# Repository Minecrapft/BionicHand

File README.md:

# Robohand

A simple Arduino sketch to control a robotic hand (servo-based) — provided as `Robohand.ino`.

## Summary

This project contains an Arduino sketch that reads inputs (sensors/buttons/potentiometers) and drives servos to move a robotic hand. Use this README to set up the hardware, upload the sketch, and customize pin mappings or servo ranges.

## Files

- `Robohand.ino` — main Arduino sketch (open in Arduino IDE).

## Required Hardware

- Arduino board (Uno, Nano, Mega, etc.)
- 3–5 x hobby servos (depending on hand design)
- Power supply for servos (separate 5–6V recommended)
- Jumper wires, breadboard
- Optional: potentiometers, push buttons, flex sensors for control

## Wiring (example)

- Connect servo signal wires to Arduino digital pins (example):
  - Thumb: D3
  - Index: D5
  - Middle: D6
  - Ring: D9
  - Pinky: D10
- Connect servo power (V+) and ground to the servo power supply. Connect servo ground to Arduino GND.
- Connect control inputs (potentiometers or buttons) to analog pins A0–A2 as needed.

Adjust pin numbers in `Robohand.ino` to match your wiring.

## Software & Upload

1. Install the Arduino IDE from https://arduino.cc.
2. Open `Robohand.ino` in the Arduino IDE.
3. Select the correct board and port under `Tools` → `Board` / `Port`.
4. Connect the Arduino via USB and click Upload.

If using external servo power, ensure the external supply is connected and common-grounded with the Arduino before powering servos.

## Usage

- Once uploaded, control the hand using the configured inputs (potentiometers/buttons). The sketch maps inputs to servo positions; modify the mapping in the code if needed.

## Customization

- Open `Robohand.ino` and edit pin definitions and servo limits to match your hardware.
- Calibrate servo min/max values to prevent mechanical binding.

## Troubleshooting

- Servos jittering: provide a stable external power supply and common ground.
- Servo not moving: check signal pin, correct power, and that the sketch references the correct pin.

## Contact

If you want help customizing the sketch or wiring, open an issue or reply here.

## ESP32-S3 (connection & run)

This sketch can run on an ESP32-S3-based board with a few small changes. Follow these steps to connect and upload:

1. Install ESP32 board support in the Arduino IDE:
  - Open `Tools` → `Board` → `Boards Manager` and install the "esp32" package by Espressif.
2. Power and wiring:
  - Servos typically need 5V. Use a separate 5–6V servo power supply and connect all grounds together (ESP32 GND ↔ servo power GND).
  - Connect each servo signal wire to a free ESP32-S3 GPIO. Example (change pins in the sketch to match):
    - Thumb: GPIO 18
    - Index: GPIO 19
    - Middle: GPIO 21
    - Ring: GPIO 22
    - Pinky: GPIO 23
  - Avoid pins reserved for flash/SPI (commonly GPIO6–GPIO11) and consult your board's pinout for S3-specific restrictions.
3. Library and code changes:
  - If `Robohand.ino` uses the AVR `Servo.h`, switch to an ESP32-compatible servo library such as `ESP32Servo` (install via Library Manager) or use a PWM/i2c driver (PCA9685) for many servos.
  - Update the pin definitions at the top of `Robohand.ino` to the GPIOs you wired.
  - Ensure servo pulse limits are appropriate for your servos (calibrate `min`/`max` values to avoid binding).
4. Uploading the sketch:
  - In Arduino IDE select `Tools` → `Board` → `ESP32S3 Dev Module` (or the specific board name) and the correct `Port`.
  - Click Upload. If required, press the boot/enable buttons as prompted by the IDE.
5. Troubleshooting & tips:
  - If servos twitch or reset the board, power them from a dedicated supply and keep a common ground.
  - For many servos, using a dedicated PWM driver (PCA9685) reduces load on the ESP32 and simplifies timing.
  - Use the Serial Monitor to view debug messages; set the baud rate in the sketch to match (commonly 115200).

These steps should get `Robohand.ino` running on an ESP32-S3 board. If you want, I can update `Robohand.ino` to include `ESP32Servo` examples and default ESP32 pin definitions.

## Control via Phone (Web Interface)

To control the robot hand from your phone using a web browser on the local network:

### Setup

1. **Connect ESP32-S3 to WiFi:**
   - Add WiFi credentials to `Robohand.ino`:
     ```cpp
     const char* ssid = "YOUR_WIFI_SSID";
     const char* password = "YOUR_WIFI_PASSWORD";
     ```
   - Initialize WiFi in `setup()`:
     ```cpp
     WiFi.begin(ssid, password);
     while (WiFi.status() != WL_CONNECTED) {
       delay(500);
     }
     Serial.println(WiFi.localIP());
     ```
   - Note the IP address printed to the Serial Monitor (e.g., `192.168.1.100`).

2. **Create a simple web server:**
   - Add these includes at the top of `Robohand.ino`:
     ```cpp
     #include <WiFi.h>
     #include <WebServer.h>
     ```
   - Create a WebServer instance:
     ```cpp
     WebServer server(80);  // Listen on port 80 (HTTP)
     ```
   - In `setup()`, define a handler that serves an HTML control panel:
     ```cpp
     server.on("/", HTTP_GET,  {
       String html = "<html><body style='font-family:Arial'>"
         "<h1>Robohand Control</h1>"
         "<button onclick=\"fetch('/servo?pin=18&pos=90')\">Thumb Open</button>"
         "<button onclick=\"fetch('/servo?pin=18&pos=0')\">Thumb Close</button><br>"
         "<button onclick=\"fetch('/servo?pin=19&pos=90')\">Index Open</button>"
         "<button onclick=\"fetch('/servo?pin=19&pos=0')\">Index Close</button><br>"
         "</body></html>";
       server.send(200, "text/html", html);
     });
     ```
   - Add a servo control endpoint:
     ```cpp
     server.on("/servo", HTTP_GET,  {
       int pin = server.arg("pin").toInt();
       int pos = server.arg("pos").toInt();
       // Attach servo and move to position
       // (details depend on your Servo library)
       server.send(200, "text/plain", "OK");
     });
     ```
   - Start the server in `setup()`:
     ```cpp
     server.begin();
     ```
   - In `loop()`, handle incoming requests:
     ```cpp
     server.handleClient();
     ```

3. **Access from your phone:**
   - Connect your device to the **`RoboHand-S3`** WiFi network (password: `12345678`).
   - Open a web browser and navigate to: **`http://192.168.4.1`**
   - No port number needed — it runs on port 80 (standard HTTP), so the browser uses it automatically.
   - You should see the Robohand control panel with buttons to open/close fingers.

4. **Customize the web interface:**
   - Add sliders for smooth servo control:
     ```html
     <input type="range" min="0" max="180" value="90" 
       onchange="fetch('/servo?pin=18&pos=' + this.value)">
     ```
   - Add visual feedback (color change, status display) using JavaScript.

### Troubleshooting

- **Phone can't find the ESP32:** Ensure both phone and ESP32-S3 are on the same WiFi network.
- **Web page doesn't load:** Check the IP address from the Serial Monitor (e.g., 192.168.1.), and make sure no firewall is blocking port 80.
- **Servos don't respond:** Verify the `/servo` endpoint is correctly wired to your servo control code.

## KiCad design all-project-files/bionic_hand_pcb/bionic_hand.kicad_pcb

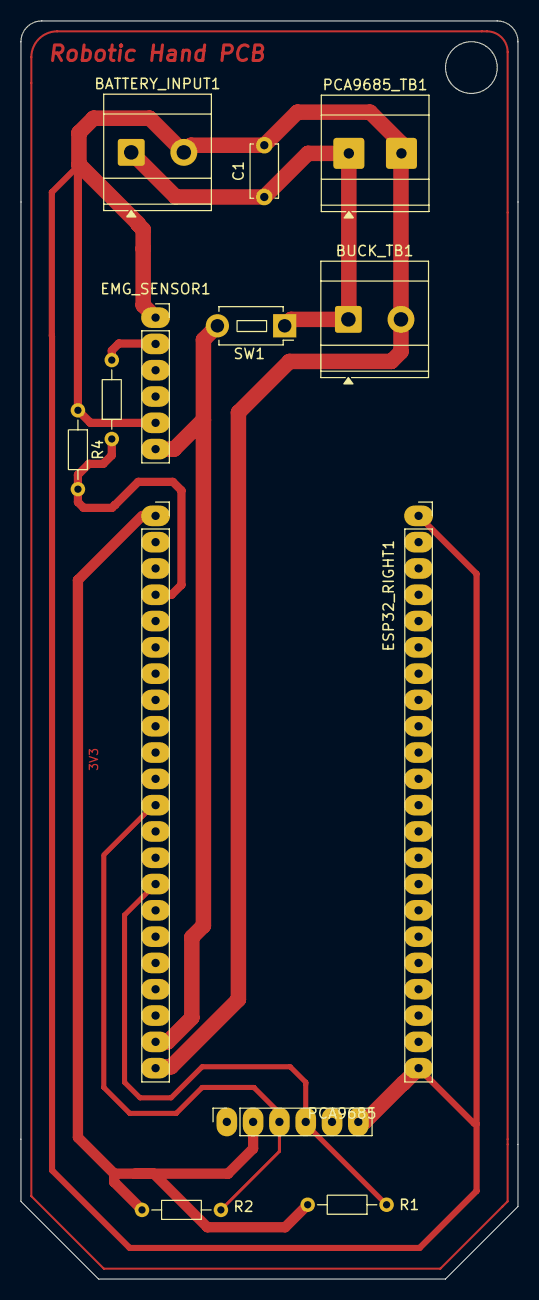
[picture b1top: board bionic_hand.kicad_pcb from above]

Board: 2 copper layers, 48.0 x 121.5 mm, 13 parts (0 on the bottom side), 7 nets.

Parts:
BATTERY_INPUT1: Screw_Terminal_01x02; TerminalBlock_MetzConnect_Type073_RT02602HBLU_1x02_P5.08mm_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
BUCK_TB1: Screw_Terminal_01x02; TerminalBlock_MetzConnect_Type073_RT02602HBLU_1x02_P5.08mm_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
C1: 470u; C_Disc_D5.0mm_W2.5mm_P5.00mm
EMG_SENSOR1: Conn_01x06; PinSocket_1x06_P2.54mm_Vertical
ESP32_LEFT1, ESP32_RIGHT1: Conn_01x22; PinSocket_1x22_P2.54mm_Vertical
PCA9685: Conn_01x06; PinSocket_1x06_P2.54mm_Vertical
PCA9685_TB1: Screw_Terminal_01x02; TerminalBlock_MetzConnect_Type073_RT02602HBLU_1x02_P5.08mm_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
R1, R2, R3: 10k; R_Axial_DIN0204_L3.6mm_D1.6mm_P7.62mm_Horizontal
R4: 20k; R_Axial_DIN0204_L3.6mm_D1.6mm_P7.62mm_Horizontal
SW1: SW_DPST_x2; SW_PUSH_1P1T_6x3.5mm_H4.3_APEM_MJTP1243

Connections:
3V3: ESP32_LEFT1.1, PCA9685.2, R1.2, R2.2
5Vin: BATTERY_INPUT1.1, BUCK_TB1.1, C1.1, EMG_SENSOR1.6, ESP32_LEFT1.21, PCA9685_TB1.1, SW1.1 (A), SW1.2 (B)
/SIG: EMG_SENSOR1.2, R3.2
CMN_GND: BATTERY_INPUT1.2, BUCK_TB1.2, C1.2, EMG_SENSOR1.1, EMG_SENSOR1.5, ESP32_LEFT1.22, ESP32_RIGHT1.1, ESP32_RIGHT1.22, PCA9685.6, PCA9685_TB1.2, R4.1
GPIO4: ESP32_LEFT1.4, R3.1, R4.2
GPIO8: ESP32_LEFT1.12, PCA9685.3, R2.1
GPIO9: ESP32_LEFT1.15, PCA9685.4, R1.1

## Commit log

2026-06-02 deleted a line
2026-06-02 Update README.md for project details and ESP32 support
2026-06-03 Create project-files
2026-06-03 Create here
2026-06-03 added the files
